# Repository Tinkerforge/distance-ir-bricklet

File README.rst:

Distance IR Bricklet
====================

This repository contains the firmware source code and the hardware design
files. The documentation generator configs can be found at
https://github.com/Tinkerforge/generators

Repository Content
------------------

software/:
 * examples/: Examples for all supported languages
 * build/: Compiled files
 * src/: Source code of firmware
 * Makefile: Makefile to build project

hardware/:
 * Contains KiCad project files and additionally schematics as PDF

datasheets/:
 * Contains datasheets for sensors and complex ICs that are used

Hardware
--------

The hardware is designed with the open source EDA Suite KiCad
(http://www.kicad.org). Before you are able to open the files,
you have to install the Tinkerforge kicad-libraries
(https://github.com/Tinkerforge/kicad-libraries). You can either clone
them directly in hardware/ or clone them in a separate folder and
symlink them into hardware/
(ln -s kicad_path/kicad-libraries project_path/hardware). After that you
can open the .pro file in hardware/ with KiCad and from there view and
modify the schematics and the PCB layout.

Software
--------

If you want to do your own Brick/Bricklet firmware development we highly
recommend that you use our build environment setup script and read the
tutorial (https://www.tinkerforge.com/en/doc/Tutorials/Tutorial_Build_Environment/Tutorial.html).

To compile the C code we recommend you to install the newest GNU Arm Embedded
Toolchain (https://launchpad.net/gcc-arm-embedded/+download).
You also need to install bricklib (https://github.com/Tinkerforge/bricklib)
and brickletlib (https://github.com/Tinkerforge/brickletlib).

You can either clone it directly in software/src/ or clone it in a
separate folder and symlink it into software/src/
(ln -s bricklib_path/bricklib project_path/software/src/ and
ln -s brickletlib_path/brickletlib project_path/software/src/).
Finally make sure to have CMake installed
(http://www.cmake.org/cmake/resources/software.html).

After that you can build the firmware by invoking make in software/.
The firmware (.bin) can then be found in software/build/ and uploaded
with brickv (click button "Flashing" on start screen).

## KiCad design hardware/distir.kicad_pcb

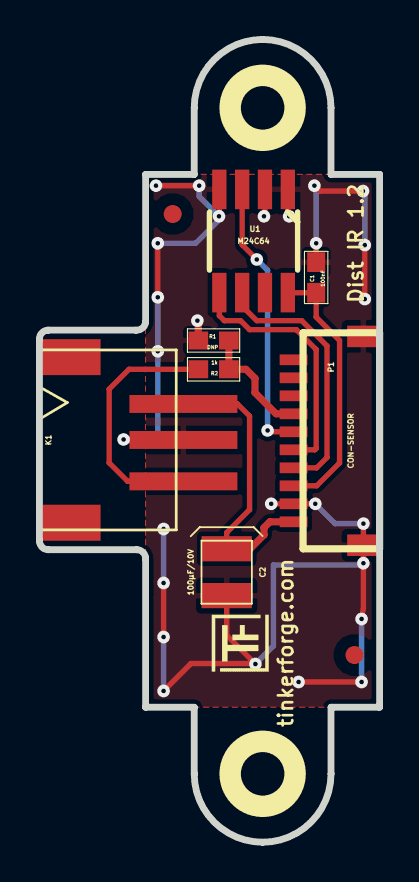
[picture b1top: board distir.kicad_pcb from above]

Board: 2 copper layers, 18.9 x 44.6 mm, 14 parts (0 on the bottom side), 8 nets.

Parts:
C1: 100nF; 0603E
C2: 100µF/10V; 3528-21
Fiducial_Mark: VAL**; Fiducial_Mark
Fiducial_Mark#2: VAL**; Fiducial_Mark
K1: S3B-PH-SM4
P1: CON-SENSOR
R1: DNP; 0603E
R2: 1k; 0603E
Ref**: Val**; Logo_31x31
U1: M24C64; SO-8
U2, U3: DRILL; DRILL_NP
VAL: WEEE_7mm
VAL#2: CE_5mm

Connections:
GND: C1.1, C2.2, K1.2, P1.2, P1.EP, R1.2, U1.1, U1.2, U1.4
IN_1: P1.7, R1.1, R2.2
unnamed: C2.1, K1.1, P1.1
unnamed: K1.3, R2.1
unnamed: P1.6, U1.3
SCL: P1.4, U1.6
SDA: P1.5, U1.5
VCC: C1.2, P1.3, U1.8

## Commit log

2011-08-25 initial hardware source commit
2011-08-25 add project description
2011-09-05 Remove offset because of better optimization in newer gccs
2011-09-13 add java bindings and examples
2011-09-14 limit line length of java examples to 100 characters
2011-09-23 Add C# examples and bindings
2011-10-05 Remove Bindings and IP Connection (these are generated and they change too often) and rename bindings to examples
2011-10-05 add tinkerforge package to python imports
2011-10-06 remove faulty gcc commandline invocation
2011-10-06 add firmware version and name
2012-02-13 update to version 1.1 - remove resistor for address data line - add fiducials on board
2012-02-14 add compatability for different tick types
2012-02-15 Add changelog
2012-02-15 Move software changelog to software folder
2012-04-25 Unify capitalization of "IP connection" in examples
2012-05-09 Add PHP examples
2012-05-14 java: Remove unnecessary new String(...) calls
2012-05-20 Use moving average instead of simple average
2012-05-25 Add Ruby examples
2012-06-05 Fix register_callback syntax error in Ruby examples on Windows
2012-06-12 Use correct term 'Bricklet' in example code error message
2012-06-12 Prefer IPConnection destroy over join_thread
2012-07-01 Add generate_makefile.bat for windows
2012-07-25 Add Delphi examples
2012-08-08 delphi: Add comment about UID
2012-09-07 Add datasheet for GP2Y0A41 sensor
2012-10-24 Make cmake find the correct objcopy binary
    On some systems cmake uses the wrong objcopy binary, tell it to use
    the correct one.
2012-11-07 Copy 2D120 calibration data for 2Y0A41
    They are compatible sensors.
2012-11-13 Support for protocol 2.0
2012-11-28 Make python examples protocol 2.0 compatible
2012-11-29 Make Ruby examples Protocol 2.0 compatible
2012-11-29 Make C examples Protocol 2.0 compatible
2012-11-29 Make Java examples Protocol 2.0 compatible
2012-11-29 Make PHP examples Protocol 2.0 compatible
2012-11-29 Make Delphi/Pascal examples Protocol 2.0 compatible
2012-11-30 Fix invalid parameter checks
2012-11-30 delphi: Remove unnecessary parentheses and call destructor again
2012-12-05 Add protocol 2.0 compatability to C# bindings
2012-12-06 Fix C examples
2012-12-11 Avoid g++ warnings about missing casts in C examples
2013-01-09 Use specific device object for callbacks
2013-01-17 Make Java examples compatible to new listener approach
2013-01-28 Update outdated comment in Java example
2013-02-07 Use IPconnection disconnect explicitly in examples
2013-02-14 Fix debounce period in threshold examples
2013-02-18 Add Visual Basic .NET examples
2013-08-09 Add shell examples
2013-08-21 windows: Don't trigger a build in generate_makefile.bat
    Also use normal make instead of a special named one.
2013-10-15 Add I2C mutex for lookup table write function
2013-10-15 Add changelog and new version
2013-11-05 Revert "Add changelog and new version"
    This reverts commit bcccaaa99dbb36c27722f3025d966266c1e9648c.
2013-11-05 Revert "Add I2C mutex for lookup table write function"
    This reverts commit f05e687e90935dd2b5086dca762e4f757af80175.
    Adding a lock call around i2c_eeprom_master_write creates a
    deadlock as i2c_eeprom_master_write already takes the I2C
    mutex. The correct fix would be to move the lock call out of
    i2c_eeprom_master_write and adapt all callers.
2013-11-05 Rebuild to pickup fix from brickletlib to avoid sending threshold callback twice
2013-12-19 Fix wrong length for GetDebounce packet (through brickletlib)
2014-01-06 Add static assert for BrickContext size
2014-01-10 Add Perl examples
2014-01-15 php: Use const for constant values
2014-02-07 Add Mathematica examples
2014-02-10 perl: fixed namespace
2014-02-12 javascript: add examples
2014-02-18 javascript: examples fixed
2014-02-20 javascript: add html examples
2014-02-24 javascript: port 4280, startExample()
2014-02-28 javascript: Break long lines and cleanup whitespace
2014-03-05 Add LabVIEW examples
2014-03-06 labview: Fix wrong method call
2014-03-06 labview: Add examples in LV2010 format
2014-03-27 matlab: add examples
2014-04-02 java: Unify constants style
2014-04-02 perl: Unify print style
2014-04-17 matlab: Adapt examples to new callback style
2014-04-17 matlab: Add parentheses to make pygments happy
2014-07-15 java: Replace System.console() usage with an Eclipse compatible pattern
2014-12-02 Use ReadLine instead of ReadKey for C# example
2015-02-13 vbnet: Use ReadLine instead of ReadKey
    Because ReadKey doesn't work with a pipe as stdin on the RED Brick.
2015-03-02 windows: Stop cmake from searching for mingw32-make.exe
    Using MinGW Makefiles as generator makes cmake search for mingw32-make.exe
    which might not be installed because GnuWin32's make.exe is used instead.
2015-04-09 c: Whitespace
2015-06-24 javascript: Clean up output creation
2015-07-14 Rename datasheets
2015-07-23 Make JavaScript browser example textarea readonly
2015-07-27 Cleanup C/C++, C#, Java, Python and Ruby examples
2015-07-29 Reformat changelog
2015-08-07 Use full device class name in Python examples
2015-08-12 Fix minor warnings in C/C++ examples
2015-08-13 Use correct simple value type
2015-08-14 Fix threshold value type in Java example
2015-08-14 Cleanup Delphi examples
2015-08-18 Cleanup VB.NET examples
2015-08-19 Cleanup Perl examples
2015-09-09 Duplicate cmake call to fix bug during cmake creation
2015-09-30 Generator based example cleanup
2015-11-12 matlab: Fix callback handling for R2014a
    http://undocumentedmatlab.com/blog/matlab-callbacks-for-java-events-in-r2014a
2015-11-25 Include date and commit into changelog
2016-03-22 fix paste layers for distance ir
2016-03-22 fix sensor connection (pins swapped)
2016-03-22 add hardware file
2016-03-31 switch to smd connector
2016-05-18 c: Add missing device destroy call
2016-06-21 add errata
2016-07-01 Make the change UID comment more explicit
2017-04-13 csharp: Adapt example
2017-04-21 shell: Adapt example
2017-06-02 octave: Use javaObject instead of deprecated java_new
2017-11-06 fix edge cuts: set on grid
2017-11-08 Add 3d information (final)
2017-11-09 Add 3d model (*.step & *.FCStd)
2017-11-30 Update examples from generator
2017-12-07 mathematica: Also generate .nb files
2018-02-02 Update examples
2018-02-19 javascript: Close div tag correctly
2018-02-20 Cleanup KiCad libraries config
    Ensure LibDir=kicad-libraries and LibName1=tinkerforge.
    Remove special library.
2018-05-07 Add -fno-tree-loop-distribute-patterns compile flag, so GCC can't embed his own non-position independent memset function
2018-05-07 Fix bug in distance calculation (interpolation between lookup table values was broken)
2018-05-07 Add ref for 2.0.3
2018-05-14 Rename files
2018-05-24 perl: Use strict in examples
2018-07-11 Add Makefile with docker support
2018-07-11 Update directory structure and build instructions
2018-07-11 Remove obsolete generate_makefile scripts
2018-11-06 Add rust examples
2018-11-07 rust: Accept host names for ip connection, fix naming inconsistencies
2018-11-07 rust: Rename callback receivers.
2018-12-14 Add go examples.
2018-12-14 go: Fix printf parameters.
2018-12-18 go: Change import path.
2018-12-18 go: Change import path again.
2018-12-20 rust: Reformat examples.
2019-01-24 mqtt: Add examples.
2019-01-24 mqtt: Fix example header.
2019-01-24 mqtt: Remove executable bit in example permissions.
2019-01-24 go: Minor example fixes.
2019-01-24 mqtt: Minor example fixes.
2019-03-28 mqtt: Fix whitespace.
2019-08-22 c: Adapt to bindings changes
2020-01-13 examples: Use python3 input instead of python2 raw_input.
2020-01-13 examples: mqtt: Remove trailing whitespace.
2020-04-14 mqtt: Fix device name format
2021-10-25 Update KiCad link
    https://www.kicad.org/blog/2021/10/Avoid-links-to-former-kicad-domain/
2022-07-06 Add license files.

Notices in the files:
hardware/distir.kicad_pcb:
Licensed under CERN OHL v.1.1
Copyright (©) 2016, B.Nordmeyer
Copyright Tinkerforge GmbH 2011.
This documentation describes Open Hardware and is licensed under the
CERN OHL v. 1.1.
